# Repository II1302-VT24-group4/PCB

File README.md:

# 🚀 Welcome to the Custom PCB Repository!

This repository has all things related to our custom printed circuit boards (PCBs), designed with KiCad.

## 🎯 Info

This repository contains three unique PCB designs, each contributed by a member of our team that studies TIEDB.

## 📚 PCB Designs

1. [**Christoffer Franzén**](https://github.com/II1302-VT24-group4/PCB/releases/tag/PCB)
2. [**Erik Heiskanen**](https://github.com/II1302-VT24-group4/PCB/releases/tag/PCB)
3. [**Hein Lee**](https://github.com/II1302-VT24-group4/PCB/releases/tag/PCB)

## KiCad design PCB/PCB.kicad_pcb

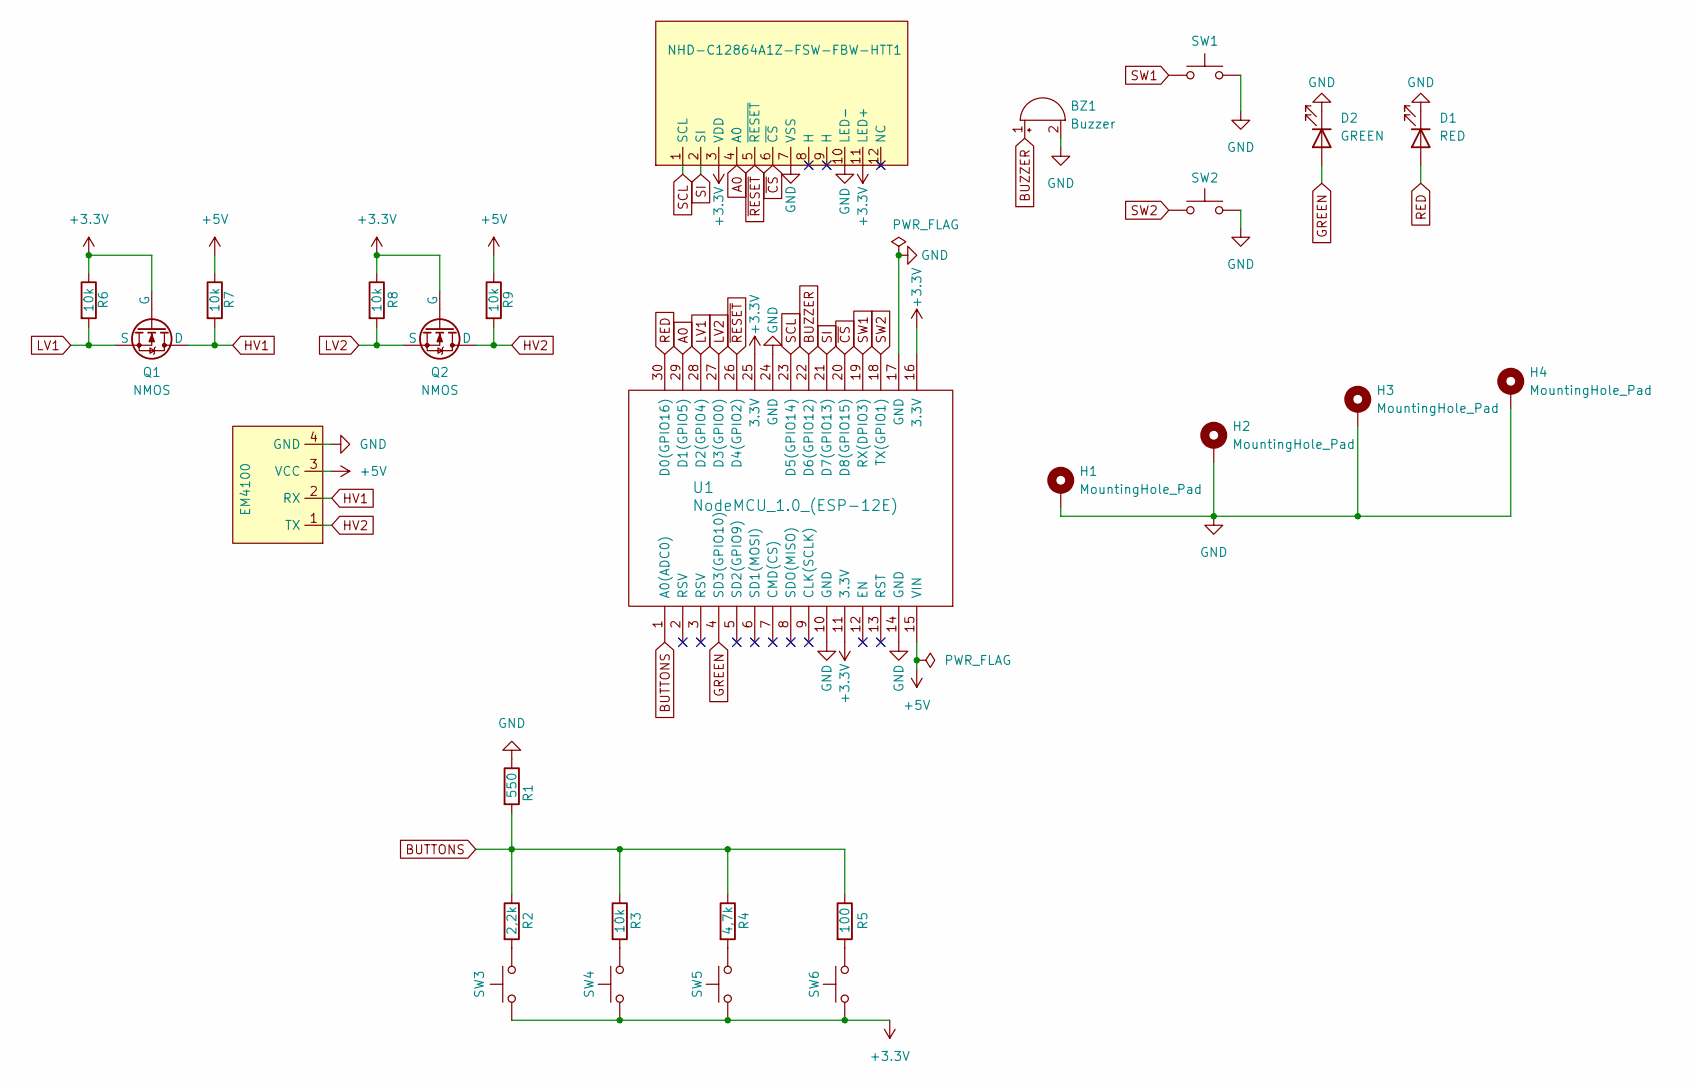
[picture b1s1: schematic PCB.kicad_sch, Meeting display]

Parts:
BZ1: Buzzer; Buzzer_12x9.5RM7.6
D1: RED; LED_D5.0mm
D2: GREEN; LED_D5.0mm
EM4100: NS-Tech_Grove_1x04_P2mm_Vertical
H1, H2, H3, H4: MountingHole_Pad; MountingHole_3.2mm_M3_Pad
NHD-C12864A1Z-FSW-FBW-HTT1: NHD
Q1, Q2: NMOS; TO-92
R1: 550; R_Axial_DIN0207_L6.3mm_D2.5mm_P7.62mm_Horizontal
R2: 2,2k; R_Axial_DIN0207_L6.3mm_D2.5mm_P7.62mm_Horizontal
R3, R6, R7, R8, R9: 10k; R_Axial_DIN0207_L6.3mm_D2.5mm_P7.62mm_Horizontal
R4: 4,7k; R_Axial_DIN0207_L6.3mm_D2.5mm_P7.62mm_Horizontal
R5: 100; R_Axial_DIN0207_L6.3mm_D2.5mm_P7.62mm_Horizontal
SW1, SW2, SW3, SW4, SW5, SW6: SW_Push; SW_BUTT-2
U1: NodeMCU_1.0_(ESP-12E); NodeMCU

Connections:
+3.3V: NHD-C12864A1Z-FSW-FBW-HTT1.3 (VDD), NHD-C12864A1Z-FSW-FBW-HTT1.11 (LED+), Q1.2 (G), Q2.2 (G), R6.1, R8.1, SW3.1, SW4.1, SW5.1, SW6.1, U1.11 (3.3V), U1.16 (3.3V), U1.25 (3.3V); also elsewhere on the board
+5V: EM4100.3 (VCC), R7.1, R9.1, U1.15 (VIN)
A0: NHD-C12864A1Z-FSW-FBW-HTT1.4 (A0), U1.29 (D1(GPIO5)); also elsewhere on the board
BUTTONS: R1.2, R2.1, R3.1, R4.1, R5.1, U1.1 (A0(ADC0))
BUZZER: BZ1.1 (+), U1.22 (D6(GPIO12))
GND: BZ1.2 (-), D1.1 (K), D2.1 (K), EM4100.4 (GND), H1.1, H2.1, H3.1, H4.1, NHD-C12864A1Z-FSW-FBW-HTT1.7 (VSS), NHD-C12864A1Z-FSW-FBW-HTT1.10 (LED-), R1.1, SW1.2, SW2.2, U1.10 (GND), U1.14 (GND), U1.17 (GND), U1.24 (GND); also elsewhere on the board
GREEN: D2.2 (A), U1.4 (SD3(GPIO10))
HV1: EM4100.2 (RX), Q1.1 (D), R7.2
HV2: EM4100.1 (TX), Q2.1 (D), R9.2
LV1: Q1.3 (S), R6.2, U1.28 (D2(GPIO4))
LV2: Q2.3 (S), R8.2, U1.27 (D3(GPIO0))
unnamed: R2.2, SW3.2
unnamed: R3.2, SW4.2
unnamed: R4.2, SW5.2
unnamed: R5.2, SW6.2
RED: D1.2 (A), U1.30 (D0(GPIO16))
SCL: NHD-C12864A1Z-FSW-FBW-HTT1.1 (SCL), U1.23 (D5(GPIO14)); also elsewhere on the board
SI: NHD-C12864A1Z-FSW-FBW-HTT1.2 (SI), U1.21 (D7(GPIO13)); also elsewhere on the board
SW1: SW1.1, U1.19 (RX(DPIO3))
SW2: SW2.1, U1.18 (TX(GPIO1))
~CS: NHD-C12864A1Z-FSW-FBW-HTT1.6 (~CS), U1.20 (D8(GPIO15)); also elsewhere on the board
~RESET: NHD-C12864A1Z-FSW-FBW-HTT1.5 (~RESET), U1.26 (D4(GPIO2)); also elsewhere on the board

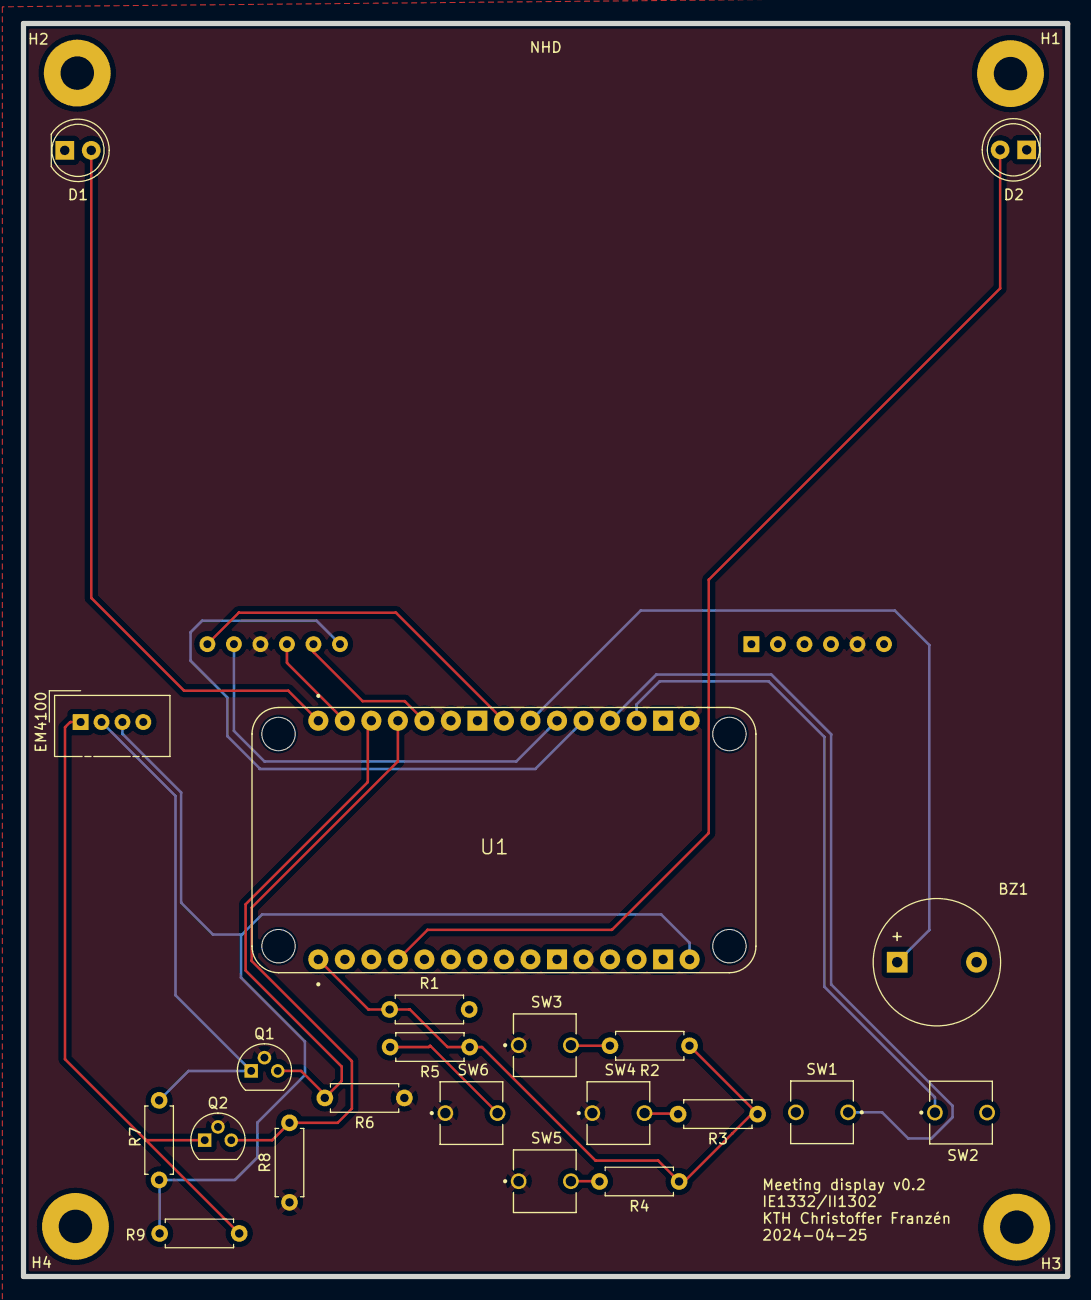
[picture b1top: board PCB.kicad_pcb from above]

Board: 2 copper layers, 100.0 x 120.0 mm, 27 parts (0 on the bottom side), 22 nets.

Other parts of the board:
NHD: NHD

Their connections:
+3.3V: NHD.3 (VDD), NHD.11 (LED+); also elsewhere on the board
A0: NHD.4 (A0); also elsewhere on the board
GND: NHD.7 (VSS), NHD.10 (LED-); also elsewhere on the board
SCL: NHD.1 (SCL); also elsewhere on the board
SI: NHD.2 (SI); also elsewhere on the board
~CS: NHD.6 (~CS); also elsewhere on the board
~RESET: NHD.5 (~RESET); also elsewhere on the board

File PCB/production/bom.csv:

Designator,Footprint,Quantity,Value,LCSC Part #
BZ1,Buzzer_12x9.5RM7.6,1,Buzzer,
D1,LED_D5.0mm,1,RED,
D2,LED_D5.0mm,1,GREEN,
EM4100,NS-Tech_Grove_1x04_P2mm_Vertical,1,~,
NHD,NHD,1,~,
"Q1, Q2",TO-92,2,NMOS,
R1,R_Axial_DIN0207_L6.3mm_D2.5mm_P7.62mm_Horizontal,1,550,
R2,R_Axial_DIN0207_L6.3mm_D2.5mm_P7.62mm_Horizontal,1,"2,2k",
"R3, R6, R7, R8, R9",R_Axial_DIN0207_L6.3mm_D2.5mm_P7.62mm_Horizontal,5,10k,
R4,R_Axial_DIN0207_L6.3mm_D2.5mm_P7.62mm_Horizontal,1,"4,7k",
R5,R_Axial_DIN0207_L6.3mm_D2.5mm_P7.62mm_Horizontal,1,100,
"SW1, SW2, SW3, SW4, SW5, SW6",SW_BUTT-2,6,SW_Push,
U1,NodeMCU,1,NodeMCU_1.0_(ESP-12E),

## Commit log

2024-04-19 added kicad files
2024-04-19 updated scematic and added footprints
2024-04-22 added my version
2024-04-22 version 0.2 removed resistor and 3v run
2024-04-22 added screen and button footprints
2024-04-22 minor tweek and started with PCB layout
2024-04-23 started PCB drawing
2024-04-23 done pcb drawing
2024-04-23 fixed edge cuts and fixed all warnings
2024-04-24 added mounting holes and gerber files
2024-04-24 Updated schematic after CMZ feedback
2024-04-24 drawn new PCB based on feedback
2024-04-25 small fix
2024-04-25 Fixed all errors and drawn tracks on 2nd layer
2024-04-25 inital final
2024-04-25 final
2024-04-25 Create LICENSE
2024-05-08 Final Version
    Erik's final version of the PCB

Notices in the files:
PCB/PCB.kicad_pcb:
gnu.org/licenses/gpl-3.0
License: GNU v3.0
